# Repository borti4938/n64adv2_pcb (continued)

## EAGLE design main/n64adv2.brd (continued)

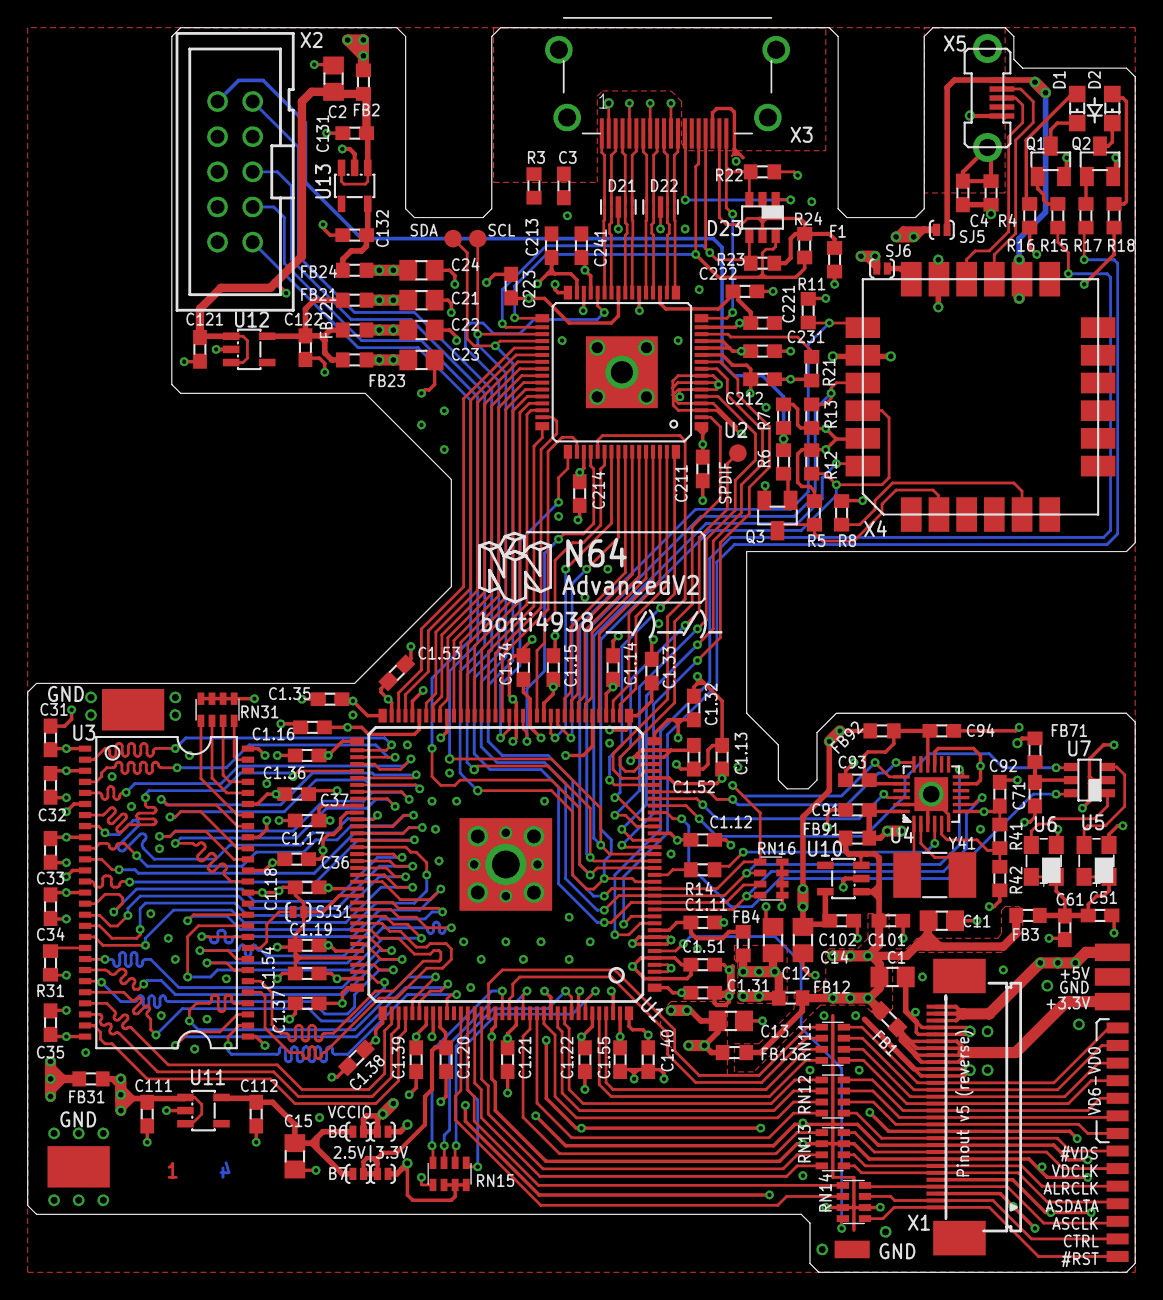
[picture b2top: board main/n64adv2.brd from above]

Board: 4 copper layers, 80.0 x 89.9 mm, 169 parts (0 on the bottom side), 177 nets.

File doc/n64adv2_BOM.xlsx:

Number of PCBs |  | 3
Designator | MPN | QTY/PCB | QTY | DESCRIPTION | VALUE | PACKAGE | NOTES | Digikey | Mouser
U1 | 10M16SAE144 | 1 | 3 | Max10 FPGA, 16k LE |  | EQFP144 | For user
 | 10M25SAE144 |  |  | Max10 FPGA, 25k LE |  | EQFP144 | For developer or as user alternative (more resources)
U2 | ADV7513BSWZ | 1 | 3 | HDMI Transmitter | ADV7513 | 48-LQFP | Aliexpress
U3 | AS4C8M16SA-xTCN | 1 | 3 | SDRAM Speicher-IC 128 Mb (8 M x 16) Parallel |  | TSOP-54 | x = Speedgrade (6 = 166MHz, 7 = 143MHz)
U4 | SI5356A-B-GMR | 1 | 3 | Clock generator |  | QFN-24
U5 | ASE-50.000MHZ-LC-T | 1 | 3 | OSC 50MHz for system pll |  | 4-SMD | L x B: 0,126" x 0,098" (3,20 mm x 2,50 mm)
 | DSC1001CI1-050.0000T |  |  |  |  |  | Alternative Part U5
U6 | ASE-24.576MHZ-LC-T | 1 | 3 | OSC 24.576MHz for audio |  | 4-SMD | L x B: 0,126" x 0,098" (3,20 mm x 2,50 mm)
 | ASEM1-24.576MHZ-LC-T |  |  |  |  |  | Alternative Part U6
U7 | 74LVC2G17DBV | 1 | 3 | Buffer gate |  | SOT-23-5 | Alternative: 74LVC1G34DBV
U10 | TLV70225DBVR | 1 | 3 | LDO 2.5V |  | SOT-23-5
U11 | TLV70025DDCR | 1 | 3 | LDO 2.5V |  | SOT-23-5 | same as U10 can be used (but not vice versa)
U12 | TLV70218DBVR | 1 | 3 | LDO 1.8V |  | SOT-23-5
U13 | TLV70033DDCR | 1 | 3 | LDO 3.3V |  | SOT-23-5
Y41 | 7A-27.000MAAJ-T | 1 | 3 | 27MHz crystal |  | 5.0X3.2
FB1,FB2,FB3,FB4,FB12,FB13,FB21,FB22,FB23,FB24,FB31,FB71,FB91,FB92 | MPZ1608S221A | 14 | 42 | Ferrit bead, power line |  | SMD0603
C1,C2 | ‎GRT21BR60J476ME13L‎ | 2 | 6 | Ceramic capacitor, X5R | 47uF / 6.3V | SMD0805
C11,C12,C13,C14,C15,C21,C22,C23,C24 | ‎CL21A106KPFNNNG‎ | 9 | 27 | Ceramic capacitor, X5R | 10uF / 6.3V | SMD0805
C101,C102,C111,C112,C121,C122,C131,C132 | ‎CL10A105KP8NNWC‎ | 8 | 24 | Ceramic capacitor, X5R | 1uF / 6.3V | SMD0603
C1.11,C1.12,C1.13,C1.14,C1.15,C1.16,C1.17,C1.18,C1.19,C1.20,C1.21,C1.22,C1.31,C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 | CL10B104KB8NNNL | 49 | 147 | Ceramic capacitor, X7R | 0.1uF / 50V | SMD0603
C51,C61 | CL10B103KB8NNNC | 2 | 6 | Ceramic capacitor, X7R | 0.01uF / 50V | SMD0603
R3 | RC0603FR-071ML | 1 | 3 | Resistor | 1M | SMD0603
R12,R13,R22 | RC0603FR-0710KL | 3 | 9 | Resistor | 10k | SMD0603
R41 | RC0603FR-073K09L | 0 | 0 | Resistor | 3k09 | SMD0603 | unpopulated, alternative values possible, ratio R41/R42 = 2 needed
R23,R24 | RC0603FR-072KL | 2 | 6 | Resistor | 2k0 | SMD0603
R42 | RC0603FR-071K58L | 1 | 3 | Resistor | 1k58 | SMD0603 | alternative values possible, ratio R41/R42 = 2 needed
R11,R15,R17,R31 | RC0603FR-071KL | 4 | 12 | Resistor | 1k0 | SMD0603
R21 | RC0603FR-07887RL | 1 | 3 | Resistor | 887 | SMD0603
R5,R16,R18 | RC0603FR-07330RL | 3 | 9 | Resistor | 330 | SMD0603
R14 | RC0603FR-0733RL | 1 | 3 | Resistor | 33 | SMD0603
RN11,RN12,RN13,RN14 | BK32164M121-T | 4 | 12 | Ferrite Beads MULTILYR CHP | BD 120OHMS 25% | SMD1206
RN15,RN31 | CAY16-103J4LF | 2 | 6 | Resistor Array (4x) | 10k0 | SMD1206
RN16 | CAY16-2201F4LF | 1 | 3 | Resistor Array (4x) | 2k2 | SMD1206
F1 | MF-FSMF020X-2 | 1 | 3 | 200mA Fuse |  | SMD0603
D1 | LTST-C194KRKT | 1 | 3 | Red LED |  | SMD0805
D2 | LTST-C194KGKT | 1 | 3 | Green LED |  | SMD0805
D21,D22 | RCLAMP0524PATCT | 2 | 6 | TVS Diode |  | 10-UFDFN
 | SZESD7104MUTAG |  |  | TVS Diode |  | 10-UFDFN | Alternative
D23 | NUP4114HMR6T1G | 1 | 3 | Clamping Diode Array |  | TSOP-6
Q1,Q2 | ZXTN08400BFFTA | 2 | 6 | NPN-Transistor |  | SOT-23
X1 | 3-1734592-0 | 1 | 3 | contacts bottom, cable 0.3mm thick (flex + stiffener) |  |  | 30 pin 0.5mm flat cable connector, reverse v5 pinout, 5V & 3.3V power rail, GND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
 |  |  |  |  |  |  | only in combination with flex (see separate tab)
X2 | 30310-6002HB | 1 | 3 |  |  |  | JTAG Connector (2x5 pins in 100mil pitch; THT or SMD)
 |  |  |  |  |  |  | optional if onboard USB Blaster is used (see separate tab)
X3 | 10029449-111RLF | 1 | 3 | HDMI Connector 19pin |  |  | Full Size HDMI Connector
 | SS-53000-001 |  |  |  |  |  | Alternative
X4
GND Finger | S1761-42R | 2 | 6 | GND shield finger |  | 3,0mm x 4,5mm pad | optional

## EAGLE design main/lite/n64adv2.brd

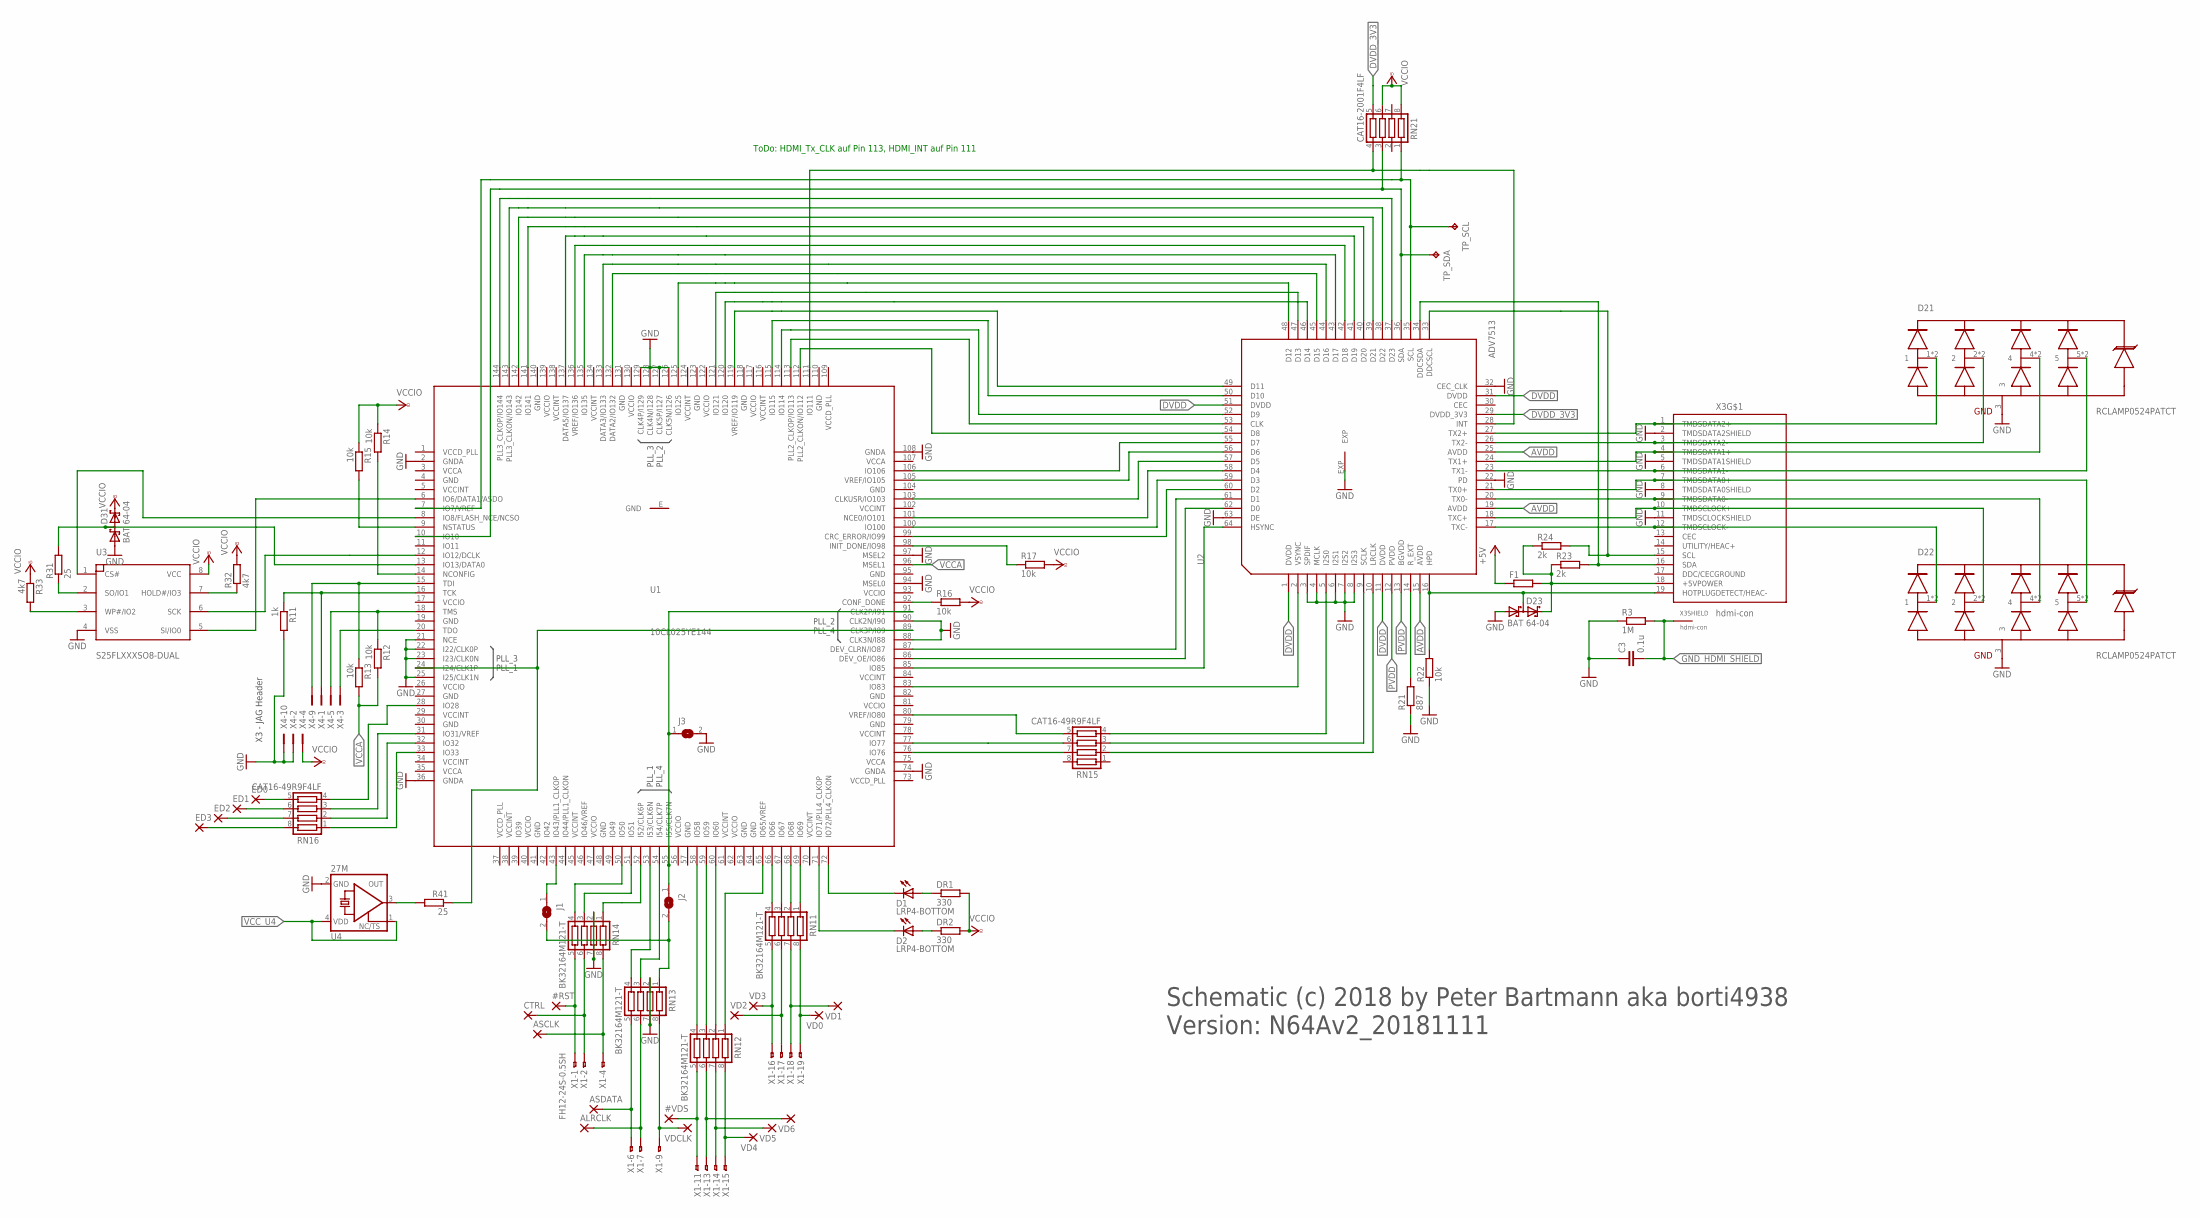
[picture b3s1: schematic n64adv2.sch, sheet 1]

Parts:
#RST: SMD1; SMD0,8-1,6
#VDS: SMD1; SMD0,8-1,6
ALRCLK: SMD1; SMD0,8-1,6
ASCLK: SMD1; SMD0,8-1,6
ASDATA: SMD1; SMD0,8-1,6
C3: 0.1u; C0603
CTRL: SMD1; SMD0,8-1,6
D1, D2: LRP4-BOTTOM; P47F-BOTTOM
D21, D22: RCLAMP0524PATCT; HDMI_RCLAMP
D23, D31: BAT 64-04; SOT23
DR1, DR2: 330; R0603
ED0, ED1, ED2, ED3: SMD1; SMD0,8-1,6
F1: R-EU_R0603; R0603
J1, J2, J3: SJSMALL; SJ_SMALL
R3: 1M; R0603
R11: 1k; R0603
R12, R13, R14, R15, R16, R17, R22: 10k; R0603
R21: 887; R0603
R23, R24: 2k; R0603
R31, R41: 25; R0603
R32, R33: 4k7; R0603
RN11, RN12, RN13, RN14: BK32164M121-T; CTS742C083
RN15, RN16: CAT16-49R9F4LF; CTS742C083
RN21: CAT16-2001F4LF; CTS742C083
TP_SCL: TPB1,27; B1,27
TP_SDA: TPB1,27; B1,27
U1: 10CL025YE144; EQFP144_2
U2: ADV7513; LQFP64_EP
U3: S25FLXXXSO8-DUAL; SO8-DUAL
U4: 27M; 3.2X2.5_KXO-V96
VD0, VD1, VD2, VD3, VD4, VD5, VD6: SMD1; SMD0,8-1,6
VDCLK: SMD1; SMD0,8-1,6
X1: FH12-24S-0.5SH
X3: hdmi-con; 685119134923
X4: 2510-; PAK100/2500-10

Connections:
+5V: F1.1; also elsewhere on the board
AVDD: U2.15 (AVDD), U2.19 (AVDD), U2.25 (AVDD); also elsewhere on the board
DVDD: U2.1 (DVDD), U2.11 (DVDD), U2.31 (DVDD), U2.51 (DVDD); also elsewhere on the board
DVDD_3V3: RN21.5, U2.29 (DVDD_3V3); also elsewhere on the board
GND: C3.1, D21.3, D22.3, D23.1 (A1), D31.1 (A1), J3.2, R3.1, R11.2, R21.1, R22.1, RN13.2, RN13.7, RN14.2, RN14.7, U1.2 (GNDA), U1.4 (GND), U1.19 (GND), U1.21 (NCE), U1.22 (I22/CLK0P), U1.23 (I23/CLK0N), U1.25 (I25/CLK1N), U1.27 (GND), U1.30 (GND), U1.36 (GNDA), U1.41 (GND), U1.48 (GND), U1.57 (GND), U1.63 (GND), U1.64 (GND), U1.74 (GNDA), U1.79 (GND), U1.82 (GND), U1.88 (CLK3N/I88), U1.90 (CLK2N/I90), U1.94 (MSEL0), U1.95 (GND), U1.97 (MSEL2), U1.104 (GND), U1.108 (GNDA), U1.110 (GND), U1.118 (GND), U1.123 (GND), U1.126 (CLK5N/I126), U1.127 (CLK5P/I127), U1.128 (CLK4N/I128), U1.129 (CLK4P/I129), U1.131 (GND), U1.140 (GND), U1.E (GND), U2.3 (SPDIF), U2.4 (MCLK), U2.6 (I2S1), U2.7 (I2S2), U2.8 (I2S3), U2.22 (PD), U2.32 (CEC_CLK), U2.63 (DE), U2.EXP, U3.4 (VSS), U4.2 (GND), X3.2 (TMDSDATA2SHIELD), X3.5 (TMDSDATA1SHIELD), X3.8 (TMDSDATA0SHIELD), X3.11 (TMDSCLOCKSHIELD), X4.2, X4.10; also elsewhere on the board
GND_HDMI_SHIELD: C3.2, R3.2, X3.SHELL (SHIELD), X3.SHELL1 (SHIELD), X3.SHELL2 (SHIELD), X3.SHELL3 (SHIELD)
unnamed: D1.A, DR1.1
unnamed: RN16.1, U1.33 (IO33)
unnamed: RN16.2, U1.32 (IO32)
unnamed: RN16.3, U1.31 (IO31/VREF)
unnamed: RN16.4, U1.28 (IO28)
unnamed: ED0.P$1, RN16.5
unnamed: ED1.P$1, RN16.6
unnamed: ED2.P$1, RN16.7
unnamed: J1.1, U1.43 (IO43/PLL1_CLKOP)
unnamed: ED3.P$1, RN16.8
unnamed: RN15.5, U1.80 (VREF/IO80)
unnamed: RN15.6, U1.77 (IO77)
unnamed: D2.C, U1.71 (IO71/PLL4_CLKOP)
unnamed: J1.2, J2.2, RN13.1
unnamed: D1.C, U1.72 (IO72/PLL4_CLKON)
unnamed: U1.85 (IO85), U2.64 (HSYNC)
unnamed: U1.83 (IO83), U2.2 (VSYNC)
unnamed: RN15.4, U2.5 (I2S0)
unnamed: RN15.3, U2.9 (SCLK)
unnamed: RN15.2, U2.10 (LRCLK)
unnamed: D23.3 (C1A2), R22.2, U2.16 (HPD), X3.19 (HOTPLUGDETECT/HEAC-)
unnamed: D22.1, D22.10 (1), U2.17 (TXC-), X3.12 (TMDSCLOCK-)
unnamed: D22.2, D22.9 (2), U2.18 (TXC+), X3.10 (TMDSCLOCK+)
unnamed: D22.4, D22.7 (4), U2.20 (TX0-), X3.9 (TMDSDATA0-)
unnamed: D22.5, D22.6 (5), U2.21 (TX0+), X3.7 (TMDSDATA0+)
unnamed: D21.5, D21.6 (5), U2.23 (TX1-), X3.6 (TMDSDATA1-)
unnamed: D21.4, D21.7 (4), U2.24 (TX1+), X3.4 (TMDSDATA1+)
unnamed: D21.2, D21.9 (2), U2.26 (TX2-), X3.3 (TMDSDATA2-)
unnamed: D21.1, D21.10 (1), U2.27 (TX2+), X3.1 (TMDSDATA2+)
unnamed: J2.1, J3.1, U1.55 (I55/CLK7N), U1.91 (CLK2P/I91)
unnamed: R24.2, U2.33 (DDCSCL), X3.15 (SCL)
unnamed: R23.2, U2.34 (DDCSDA), X3.16 (SDA)
unnamed: R21.2, U2.14 (R_EXT)
unnamed: RN21.4, U1.111 (IO111), U2.28 (INT)
unnamed: RN11.1, U1.69 (IO69)
unnamed: R31.1, U3.2 (SO/IO1)
unnamed: RN15.7, U1.76 (IO76)
unnamed: R41.2, U4.3 (OUT)
unnamed: D23.2 (C2), F1.2, R23.1, R24.1, X3.18 (+5VPOWER)
unnamed: RN11.5, VD3.P$1, X1.16
unnamed: RN11.6, VD2.P$1, X1.17
unnamed: RN11.7, VD1.P$1, X1.18
unnamed: RN11.8, VD0.P$1, X1.19
unnamed: R41.1, U1.24 (I24/CLK1P), U1.89 (CLK3P/I89)
unnamed: R17.1, U1.98 (INIT_DONE/IO98)
unnamed: RN11.2, U1.68 (IO68)
unnamed: RN12.1, U1.65 (IO65/VREF)
unnamed: RN12.2, U1.60 (IO60)
unnamed: RN12.3, U1.59 (IO59)
unnamed: RN12.4, U1.58 (IO58)
unnamed: RN12.8, VD4.P$1, X1.15
unnamed: RN12.7, VD5.P$1, X1.14
unnamed: RN12.6, VD6.P$1, X1.13
unnamed: #VDS.P$1, RN12.5, X1.11
unnamed: RN13.8, VDCLK.P$1, X1.9
unnamed: ALRCLK.P$1, RN13.6, X1.7
unnamed: ASDATA.P$1, RN13.5, X1.6
unnamed: RN14.1, U1.52 (I52/CLK6P)
unnamed: RN13.3, U1.54 (I54/CLK7P)
unnamed: RN13.4, U1.53 (I53/CLK6N)
unnamed: ASCLK.P$1, RN14.8, X1.4
unnamed: CTRL.P$1, RN14.6, X1.2
unnamed: #RST.P$1, RN14.5, X1.1
unnamed: RN14.4, U1.50 (IO50)
unnamed: RN14.3, U1.51 (IO51)
unnamed: RN11.3, U1.67 (IO67)
unnamed: U1.8 (IO8/FLASH_NCE/NCSO), U3.1 (CS#)
unnamed: U1.6 (IO6/DATA1/ASDO), U3.5 (SI/IO0)
unnamed: D31.3 (C1A2), R31.2, U1.13 (IO13/DATA0)
unnamed: U1.12 (IO12/DCLK), U3.6 (SCK)
unnamed: R33.2, U3.3 (WP#/IO2)
unnamed: R32.1, U3.7 (HOLD#/IO3)
unnamed: R11.1, U1.16 (TCK), X4.1
unnamed: U1.20 (TDO), X4.3
unnamed: R12.1, U1.18 (TMS), X4.5
unnamed: R13.1, U1.15 (TDI), X4.9
unnamed: RN11.4, U1.66 (IO66)
unnamed: R15.2, U1.9 (NSTATUS)
unnamed: R14.2, U1.14 (NCONFIG)
unnamed: R16.1, U1.92 (CONF_DONE)
unnamed: D2.A, DR2.1
PVDD: U2.12 (PVDD), U2.13 (BGVDD); also elsewhere on the board
SCL: RN21.1, TP_SCL.TP, U1.7 (IO7/VREF), U2.35 (SCL)
SDA: RN21.3, TP_SDA.TP, U1.10 (IO10), U2.36 (SDA)
TX_B0: U1.86 (DEV_OE/IO86), U2.62 (D0)
TX_B1: U1.87 (DEV_CLRN/IO87), U2.61 (D1)
TX_B2: U1.99 (CRC_ERROR/IO99), U2.60 (D2)
TX_B3: U1.100 (IO100), U2.59 (D3)
TX_B4: U1.101 (NCE0/IO101), U2.58 (D4)
TX_B5: U1.103 (CLKUSR/IO103), U2.57 (D5)
TX_B6: U1.105 (VREF/IO105), U2.56 (D6)
TX_B7: U1.106 (IO106), U2.55 (D7)
TX_CLK: U1.113 (PLL2_CLKOP/IO113), U2.53 (CLK)
TX_G0: U1.112 (PLL2_CLKON/IO112), U2.54 (D8)
TX_G1: U1.114 (IO114), U2.52 (D9)
TX_G2: U1.115 (IO115), U2.50 (D10)
TX_G3: U1.119 (VREF/IO119), U2.49 (D11)
TX_G4: U1.125 (IO125), U2.48 (D12)
TX_G5: U1.121 (IO121), U2.47 (D13)
TX_G6: U1.120 (IO120), U2.46 (D14)
TX_G7: U1.132 (DATA2/IO132), U2.45 (D15)
TX_R0: U1.133 (DATA3/IO133), U2.44 (D16)
TX_R1: U1.135 (IO135), U2.43 (D17)
TX_R2: U1.136 (VREF/IO136), U2.42 (D18)
TX_R3: U1.137 (DATA5/IO137), U2.41 (D19)
TX_R4: U1.141 (IO141), U2.40 (D20)
TX_R5: U1.142 (IO142), U2.39 (D21)
TX_R6: U1.143 (PLL3_CLKON/IO143), U2.38 (D22)
TX_R7: U1.144 (PLL3_CLKOP/IO144), U2.37 (D23)
VCCA: R12.2, R13.2, U1.3 (VCCA), U1.35 (VCCA), U1.75 (VCCA), U1.96 (MSEL1), U1.107 (VCCA); also elsewhere on the board
VCCD_PLL: U1.1 (VCCD_PLL), U1.37 (VCCD_PLL), U1.73 (VCCD_PLL), U1.109 (VCCD_PLL); also elsewhere on the board
VCCINT: U1.5 (VCCINT), U1.29 (VCCINT), U1.34 (VCCINT), U1.38 (VCCINT), U1.45 (VCCINT), U1.61 (VCCINT), U1.70 (VCCINT), U1.78 (VCCINT), U1.84 (VCCINT), U1.102 (VCCINT), U1.116 (VCCINT), U1.124 (VCCINT), U1.134 (VCCINT), U1.138 (VCCINT); also elsewhere on the board
VCCIO: D31.2 (C2), DR1.2, DR2.2, R14.1, R15.1, R16.2, R17.2, R32.2, R33.1, RN21.6, RN21.8, U1.17 (VCCIO), U1.26 (VCCIO), U1.40 (VCCIO), U1.47 (VCCIO), U1.56 (VCCIO), U1.62 (VCCIO), U1.81 (VCCIO), U1.93 (VCCIO), U1.117 (VCCIO), U1.122 (VCCIO), U1.130 (VCCIO), U1.139 (VCCIO), U3.8 (VCC), X4.4; also elsewhere on the board
VCC_U4: U4.1 (TS), U4.4 (VDD); also elsewhere on the board

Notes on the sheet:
X3 - JAG Header
Schematic (c) 2018 by Peter Bartmann aka borti4938 Version: N64Av2_20181111
ToDo: HDMI_Tx_CLK auf Pin 113, HDMI_INT auf Pin 111

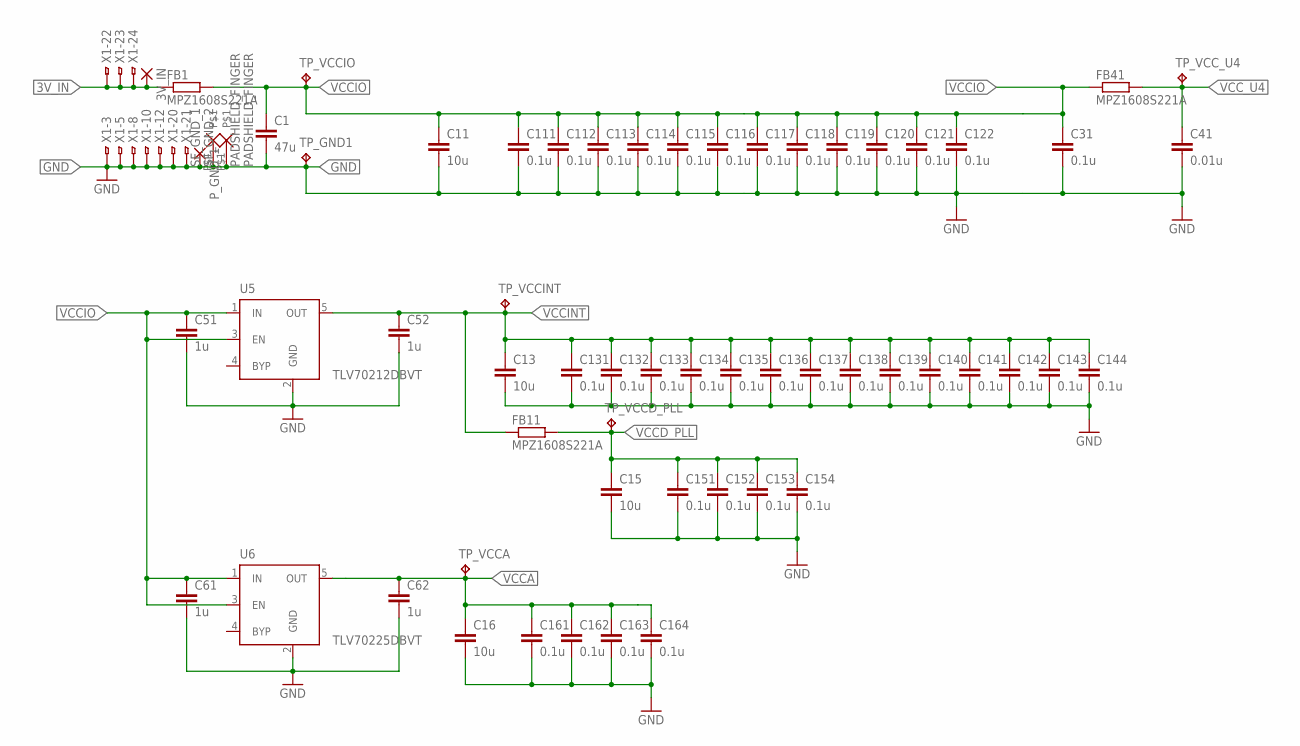
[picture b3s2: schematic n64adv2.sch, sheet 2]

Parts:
3V_IN: SMD2; SMD1,27-2,54
C1: 47u; C0805
C11, C13, C15, C16: 10u; C0805
C31, C111, C112, C113, C114, C115, C116, C117, C118, C119, C120, C121, C122, C131, C132, C133, C134, C135, C136, C137, C138, C139, C140, C141, C142, C143, C144, C151, C152, C153, C154, C161, C162, C163, C164: 0.1u; C0603
C41: 0.01u; C0603
C51, C52, C61, C62: 1u; C0603
FB1, FB11, FB41: MPZ1608S221A; R0603
P_GND_1: SMD2; SMD1,27-2,54
SF_GND_1, SF_GND_2: PADSHIELD_FINGER; GND_FINGER_PAD
TP_GND1: TPB1,27; B1,27
TP_VCCA: TPB1,27; B1,27
TP_VCCD_PLL: TPB1,27; B1,27
TP_VCCINT: TPB1,27; B1,27
TP_VCCIO: TPB1,27; B1,27
TP_VCC_U4: TPB1,27; B1,27
U5: TLV70212DBVT; SOT23-5
U6: TLV70225DBVT; SOT23-5
X1: FH12-24S-0.5SH

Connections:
3V_IN: 3V_IN.1, FB1.1, X1.22, X1.23, X1.24
GND: C1.2, C11.2, C13.2, C15.2, C16.2, C31.2, C41.2, C51.2, C52.2, C61.2, C62.2, C111.2, C112.2, C113.2, C114.2, C115.2, C116.2, C117.2, C118.2, C119.2, C120.2, C121.2, C122.2, C131.2, C132.2, C133.2, C134.2, C135.2, C136.2, C137.2, C138.2, C139.2, C140.2, C141.2, C142.2, C143.2, C144.2, C151.2, C152.2, C153.2, C154.2, C161.2, C162.2, C163.2, C164.2, P_GND_1.1, SF_GND_1.P$1, SF_GND_2.P$1, TP_GND1.TP, U5.2 (GND), U6.2 (GND), X1.3, X1.5, X1.8, X1.10, X1.12, X1.20, X1.21; also elsewhere on the board
VCCA: C16.1, C62.1, C161.1, C162.1, C163.1, C164.1, TP_VCCA.TP, U6.5 (OUT); also elsewhere on the board
VCCD_PLL: C15.1, C151.1, C152.1, C153.1, C154.1, FB11.2, TP_VCCD_PLL.TP; also elsewhere on the board
VCCINT: C13.1, C52.1, C131.1, C132.1, C133.1, C134.1, C135.1, C136.1, C137.1, C138.1, C139.1, C140.1, C141.1, C142.1, C143.1, C144.1, FB11.1, TP_VCCINT.TP, U5.5 (OUT); also elsewhere on the board
VCCIO: C1.1, C11.1, C31.1, C51.1, C61.1, C111.1, C112.1, C113.1, C114.1, C115.1, C116.1, C117.1, C118.1, C119.1, C120.1, C121.1, C122.1, FB1.2, FB41.1, TP_VCCIO.TP, U5.1 (IN), U5.3 (EN), U6.1 (IN), U6.3 (EN); also elsewhere on the board
VCC_U4: C41.1, FB41.2, TP_VCC_U4.TP; also elsewhere on the board

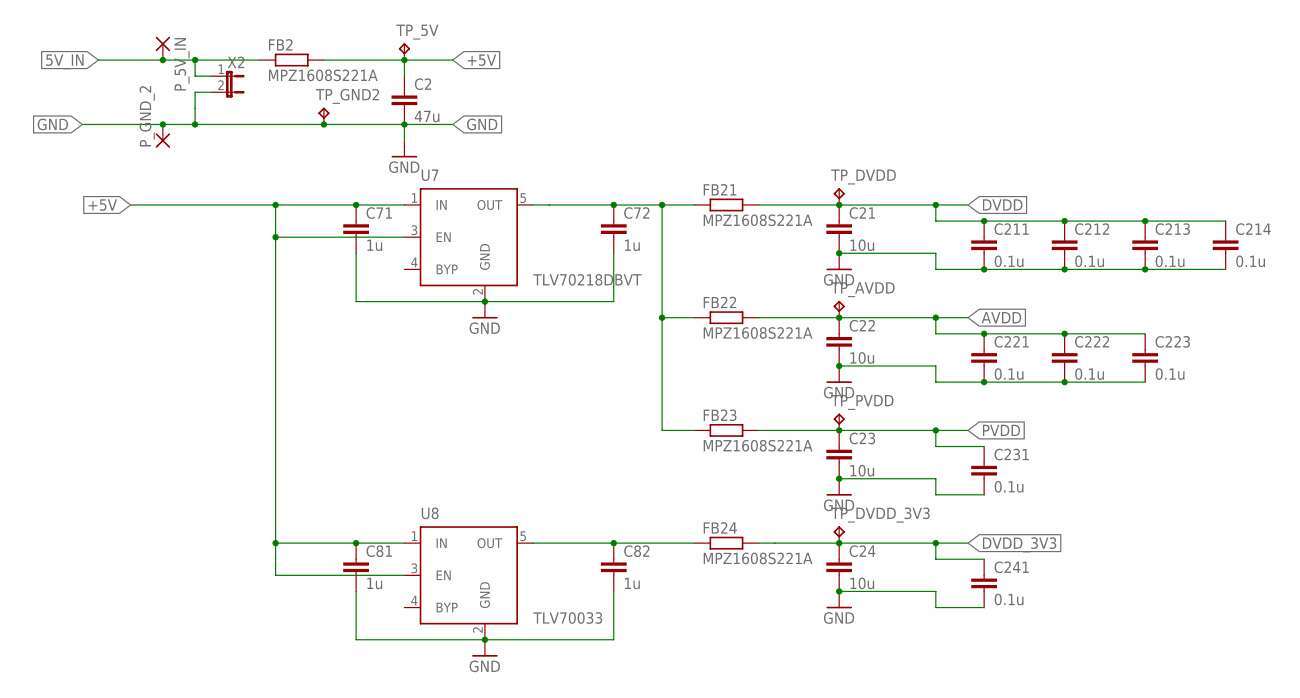
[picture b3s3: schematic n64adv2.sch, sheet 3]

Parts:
C2: 47u; C0805
C21, C22, C23, C24: 10u; C0805
C71, C72, C81, C82: 1u; C0603
C211, C212, C213, C214, C221, C222, C223, C231, C241: 0.1u; C0603
FB2, FB21, FB22, FB23, FB24: MPZ1608S221A; R0603
P_5V_IN: SMD2; SMD1,27-2,54
P_GND_2: SMD2; SMD1,27-2,54
TP_5V: TPB1,27; B1,27
TP_AVDD: TPB1,27; B1,27
TP_DVDD: TPB1,27; B1,27
TP_DVDD_3V3: TPB1,27; B1,27
TP_GND2: TPB1,27; B1,27
TP_PVDD: TPB1,27; B1,27
U7: TLV70218DBVT; SOT23-5
U8: TLV70033; SOT23-5
X2: JP1E; JP1

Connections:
1.8V_PRE: C72.1, FB21.1, FB22.1, FB23.1, U7.5 (OUT)
3.3V_PRE: C82.1, FB24.1, U8.5 (OUT)
5V_IN: FB2.1, P_5V_IN.1, X2.1
+5V: C2.1, C71.1, C81.1, FB2.2, TP_5V.TP, U7.1 (IN), U7.3 (EN), U8.1 (IN), U8.3 (EN); also elsewhere on the board
AVDD: C22.1, C221.1, C222.1, C223.1, FB22.2, TP_AVDD.TP; also elsewhere on the board
DVDD: C21.1, C211.1, C212.1, C213.1, C214.1, FB21.2, TP_DVDD.TP; also elsewhere on the board
DVDD_3V3: C24.1, C241.1, FB24.2, TP_DVDD_3V3.TP; also elsewhere on the board
GND: C2.2, C21.2, C22.2, C23.2, C24.2, C71.2, C72.2, C81.2, C82.2, C211.2, C212.2, C213.2, C214.2, C221.2, C222.2, C223.2, C231.2, C241.2, P_GND_2.1, TP_GND2.TP, U7.2 (GND), U8.2 (GND), X2.2; also elsewhere on the board
PVDD: C23.1, C231.1, FB23.2, TP_PVDD.TP; also elsewhere on the board

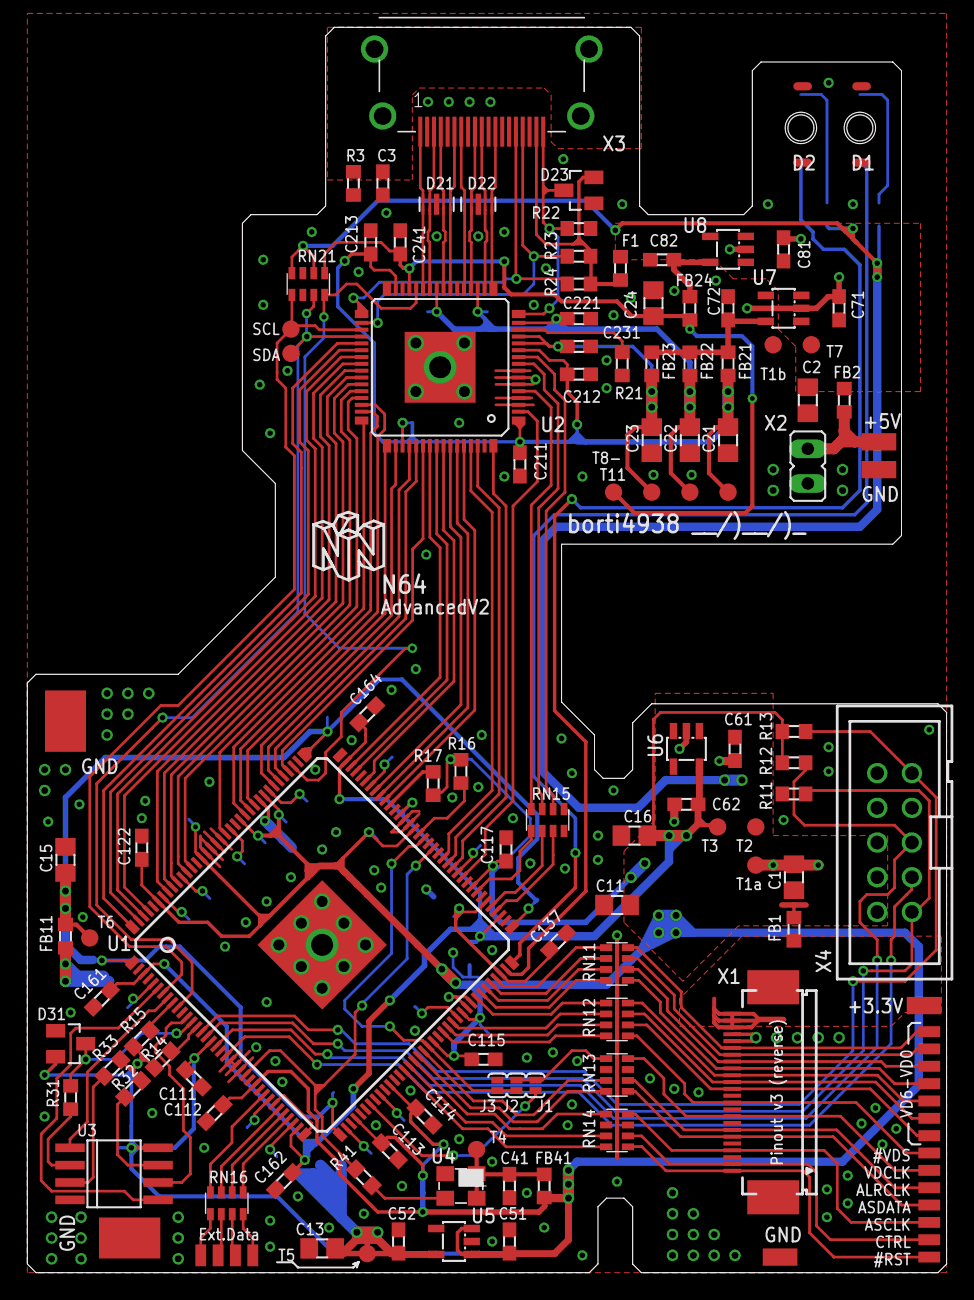
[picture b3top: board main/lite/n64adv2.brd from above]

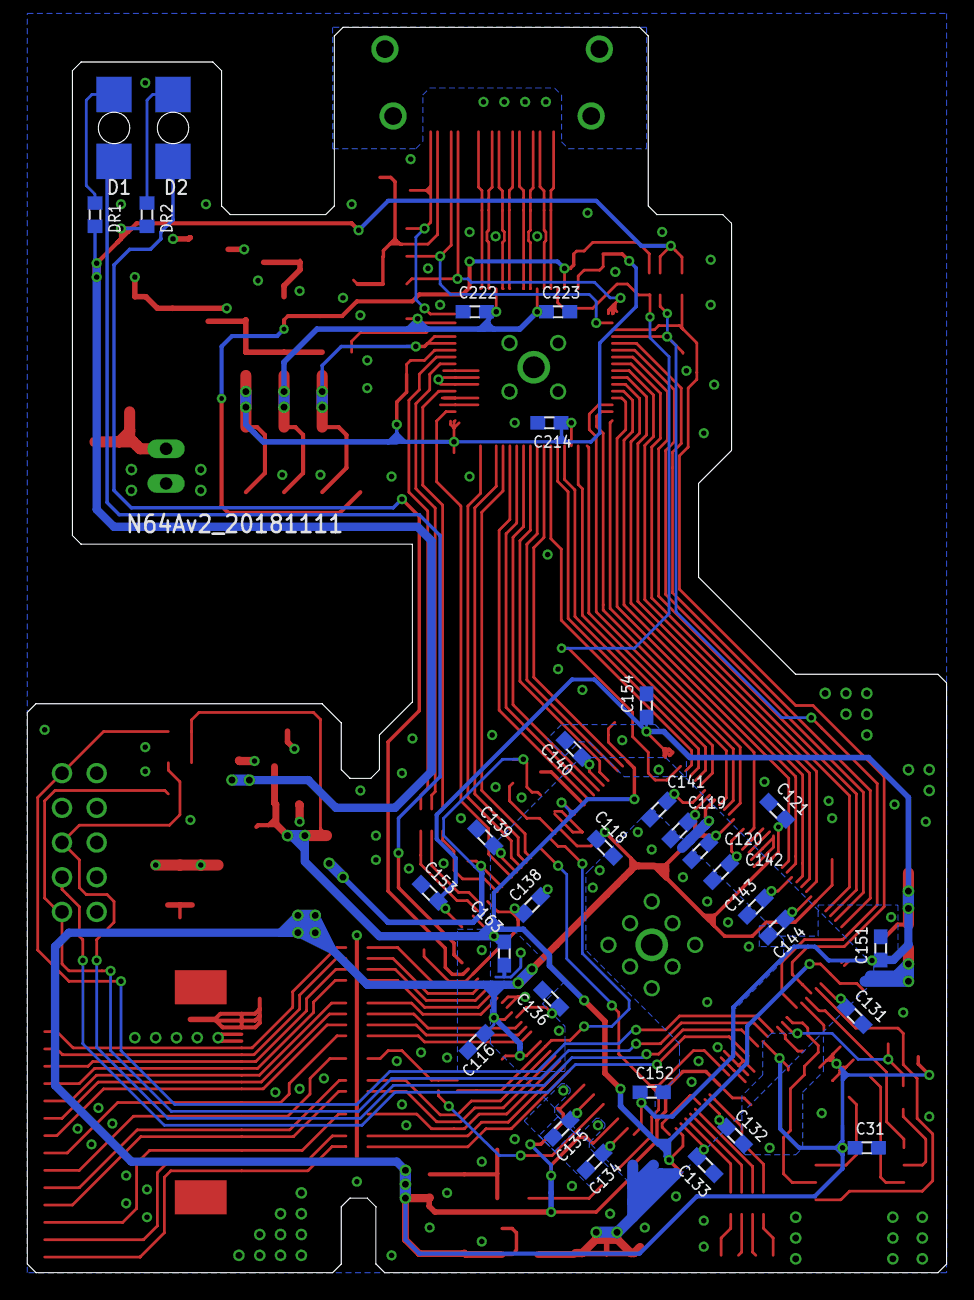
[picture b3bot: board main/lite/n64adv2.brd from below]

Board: 2 copper layers, 67.3 x 91.2 mm, 157 parts (31 on the bottom side), 124 nets.

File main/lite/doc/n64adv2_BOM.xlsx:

Designator | MPN | QTY | DESCRIPTION | VALUE | PACKAGE | NOTES | Digikey | Mouser
U1 | 10CL025YE144C8G | 1 | Cyclone 10 LP FPGA, 25k LE |  | EQFP144 | Alternative: EP4CE22E22C8N and any other application profile and/or speed grade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
U2 | ADV7513BSWZ | 1 | HDMI Transmitter | ADV7513 | 48-LQFP | found on Aliexpress
U3 | IS25LP016D-JBLE-TR | 1 | IC FLASH 16MBIT 108MHZ 8SOIC |  | 8-SOIC | 208mil Body | https://www.digikey.de/product-detail/de/issi-integrated-sil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 | https://www.mouser.de/ProductDetail/870-IS25LP016DJBLETR
U4 | ASE-27.000MHZ-LC-T | 1 | OSC 27MHz |  | 4-SMD | L x B: 0,126" x 0,098" (3,20 mm x 2,50 mm)
U5 | TLV70212DBVR | 1 | LDO 1.2V |  | SOT-23-5
U6 | TLV70225DBVR | 1 | LDO 2.5V |  | SOT-23-5
U7 | TLV70218DBVTR | 1 | LDO 1.8V |  | SOT-23-5
U8 | TLV70033DDCR | 1 | LDO 3.3V |  | SOT-23-5
FB1,FB2,FB11,FB21,FB22,FB23,FB24,FB41 | MPZ1608S221A | 8 | Ferrit bead, power line |  | SMD0603
C1,C2 | GRM21BR61A476ME15L | 2 | Ceramic capacitor, X5R | 47uF / 6.3V | SMD0805
C3,C31,C111,C112,C113,C114,C1115,C116,C117,C118,C119,C120,C121,C122,C131,C132,C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 |  | 45 | Ceramic capacitor, X7R | 0.1uF / 50V | SMD0603
C11,C13,C15,C16,C21,C22,C23,C24 | GRM21BR61C106KE15L | 8 | Ceramic capacitor, X5R | 10uF / 6.3V | SMD0805
C41 |  | 1 | Ceramic capacitor, X7R | 0.01uF / 50V | SMD0603
C51,C52,C61,C62,C71,C72,C81,C82 |  | 8 | Ceramic capacitor, X5R | 1uF / 6.3V | SMD0603
R3 | ERJ-3EKF1004V | 1 | Resistor | 1M | SMD0603
R11 | ERJ-3EKF1001V | 1 | Resistor | 1k | SMD0603
R12,R13,R14,R15,R16,R17,R22 | ERJ-3EKF1002V | 7 | Resistor | 10k | SMD0603
R21 | ERJ-3EKF8870V | 1 | Resistor | 887 | SMD0603
R23,R24 | ERJ-3EKF2001V | 2 | Resistor | 2k0 | SMD0603
R25 | ERJ-3EKF49R9V | 1 | Resistor | 49.9 | SMD0603
R31,R41 | ERJ-3EKF24R9V | 2 | Resistor | 25 | SMD0603
R32,R33 | ERJ-3EKF24R9V | 2 | Resistor | 4k7 | SMD0603
RN11,RN12,RN13,RN14 | BK32164M121-T | 4 | Ferrite Beads MULTILYR CHP | BD 120OHMS 25% | SMD1206
RN15,RN16 | CAT16-49R9F4LF / CAY16-49R9F4LF | 2 | Resistor Array (4x) | 47 | SMD1206
RN21 | CAT16-2001F4LF / CAY16-2001F4LF | 1 | Resistor Array (4x) | 2k0 | SMD1206 | Alternative: CAT16-202J4LF / CAY16-202J4LF
F1 | MF-FSMF020X-2 | 1 | 200mA Fuse |  | SMD0603
D21,D22 | RCLAMP0524PATCT | 2 | TVS Diode |  | 10-UFDFN
D23,D31 | BAT 64-04 | 2 | Clamping Diode |  | SOT23-3
D1,D2 | LR P47F-U2AB-1-1-Z | 2 | LED red |  | SMD | reverse mount
DR1,DR2 | ERJ-3EKF3300V | 2 | Resistor | 330 | SMD0603
X1 |  | 1 |  |  |  | 24 pin 0.5mm flat cable connector, reverse v3 pinout 3.3V power rail and data
X2 |  | 1 |  |  |  | 2 pin header 5V power rail
X3 | 10029449-111RLF | 1 | HDMI Connector 19pin |  |  | Full Size HDMI Connector
X4 | 30310-6002HB | 1 |  |  |  | JTAG Connector
GND Finger | S1761-42R | 2 | GND shield finger |  | 3,0mm x 4,5mm pad | optional
Summe ca. 50€ + MwSt.

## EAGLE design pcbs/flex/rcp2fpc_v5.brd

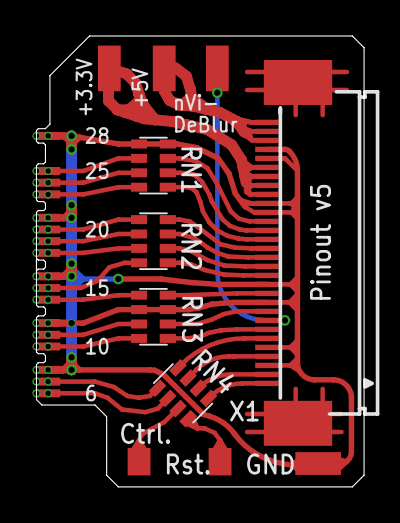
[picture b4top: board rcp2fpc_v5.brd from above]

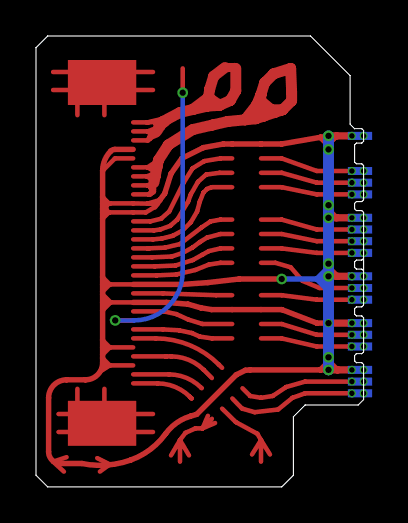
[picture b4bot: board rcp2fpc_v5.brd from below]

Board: 2 copper layers, 18.2 x 25.1 mm, 45 parts (17 on the bottom side), 32 nets.

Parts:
+3.3V, +5V: SMD1,27-2,54
E$1, E$3, E$4, E$5: CTS742C083
E$2, E$6: SMD0.8SQ
E$8, E$9, E$10, E$11, E$12, E$13, E$14, E$15, E$16, E$17, E$18, E$19, E$22, E$23, E$24, E$25, E$26, E$27, E$28, E$29, E$30, E$31, E$32, E$33, E$38, E$40, E$41, E$42, E$43, E$44, E$45, E$46, E$47: SMD0,45-1,35
E$20: FH12-30S-0.5SH
GND: SMD0,45-1,35
GND_P: SMD1,27-2,54
NVIDB: SMD1,27-2,54

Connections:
3V3: +3.3V.1, E$20.22, E$20.23, E$20.24, E$20.25
#DSYNC: E$5.1, E$10.P$1, E$31.P$1
#DSYNC.1: E$5.8, E$20.11
+5V: +5V.1, E$20.28, E$20.29, E$20.30
CTRL: E$1.7, E$2.P$1
CTRL.1: E$1.2, E$20.2
D0: E$3.2, E$19.P$1, E$22.P$1
D0.1: E$3.7, E$20.19
D1: E$3.3, E$18.P$1, E$23.P$1
D1.1: E$3.6, E$20.18
D2: E$3.4, E$17.P$1, E$24.P$1
D2.1: E$3.5, E$20.17
D3: E$4.1, E$15.P$1, E$26.P$1
D3.1: E$4.8, E$20.16
D4: E$4.2, E$14.P$1, E$27.P$1
D4.1: E$4.7, E$20.15
D5: E$4.3, E$13.P$1, E$28.P$1
D5.1: E$4.6, E$20.14
D6: E$4.4, E$11.P$1, E$30.P$1
D6.1: E$4.5, E$20.13
GND: E$3.1, E$3.8, E$5.2, E$5.7, E$9.P$1, E$12.P$1, E$16.P$1, E$20.3, E$20.5, E$20.10, E$20.12, E$20.20, E$20.21, E$20.26, E$20.27, E$25.P$1, E$29.P$1, E$32.P$1, E$46.P$1, GND_P.1
LRCLK: E$5.4, E$38.P$1
LRCLK.1: E$5.5, E$20.7
NVIDB: E$20.8, NVIDB.1
RST: E$1.8, E$6.P$1
RST.1: E$1.1, E$20.1
SCLK: E$1.6, E$41.P$1
SCLK.1: E$1.3, E$20.4
SDATA: E$1.5, E$40.P$1
SDATA.1: E$1.4, E$20.6
VCLK: E$5.3, E$8.P$1, E$33.P$1
VCLK.1: E$5.6, E$20.9

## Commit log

2021-11-14 initial commit new repository
2021-11-14 add full custom flex RCP to N64Adv2
2022-02-14 update JTAG spacer
2022-04-18 huge update: - I know: commit is too large - port main PCB to KiCad - reorganize repo structure - add README
2022-04-18 some typos
2022-04-18 add UltraPIF description
2022-07-22 update full flex: - redesign in KiCad - add trace for VI-DeBlur Feedback
2022-08-23 update flex PCB with minor changes, e.g. added a logo
2022-08-23 update main PCB with minor changes, e.g. ensure that solder mask bridges between 0.5mm pitched pads has min. 0.1mm thickness
2022-08-23 add PCB specs to README
2022-08-23 update common BOM
2022-09-05 update flex PCB: - add a feedback path for VI-Deblur - optimize implementation around U1 - add logo and license text to silkscreen
2022-09-05 add a small remark that fw needs adaptation for 16Mx16 SDRAM usage
2022-09-05 update main PCB: - optimize some trace routing - optimize component selection/placing (e.g. HDMI port full SMD, JTAG as SMD alternative) - add license to silkscreen
2022-09-05 update full BOM
2022-09-05 add changelog and license
2022-09-14 Main PCB update: - edge cuts: yet another update hopefully getting the perfect fit this time - hdmi connector position moved 0.5mm to the left - optimize mask for D21, D22, X3
2022-10-09 tiny optimizations: - change HDMI footprint a bit (increase size of shield pads) - move HDMI port a bit further on the PCB - adapt copper pour on l2 a bit
2022-11-06 reduce pad hole size at usb port and fix a gnd trace
2022-11-06 update gerbers
2022-11-12 update 3d printed models for new HDMI port
2022-11-12 update names for 3D printed parts
2022-11-20 give a bit mor space at the MultiOut stand-offs as earliest N64 models (PAL only???) seems to have thicker ones there
2022-11-20 some BOM updates
2022-12-01 fix edge cuts problem and rearrange some power supply lines near HDMI Tx
2023-05-21 update part numbers for Y41,, RN11-14
2023-11-05 update main-pcb: - remove jumper which were left overs from prototype stages - remove some test points - add pads for SPDIF near DIY-IO-Pad area
2023-11-05 Update flex-PCB: - move buffer IC to resistor array area of PCB (not on arms anymore) - add pads as backup if arms get ripped off
2023-11-26 Update main-PCB: - fixing solder mask - slightly move components a bit (USB port, JTAG, C2, ...)
2023-11-26 Update BOM
2023-11-27 protect unconnected pad at U1 by small traces
2024-01-20 leave a note and BOM for the PicoDVI-N64_PCB project by dalogue1
2024-08-08 remove BOM for PicoDVI
2024-08-08 Adjust BOM a tiny bit
2024-08-16 remove left over note
